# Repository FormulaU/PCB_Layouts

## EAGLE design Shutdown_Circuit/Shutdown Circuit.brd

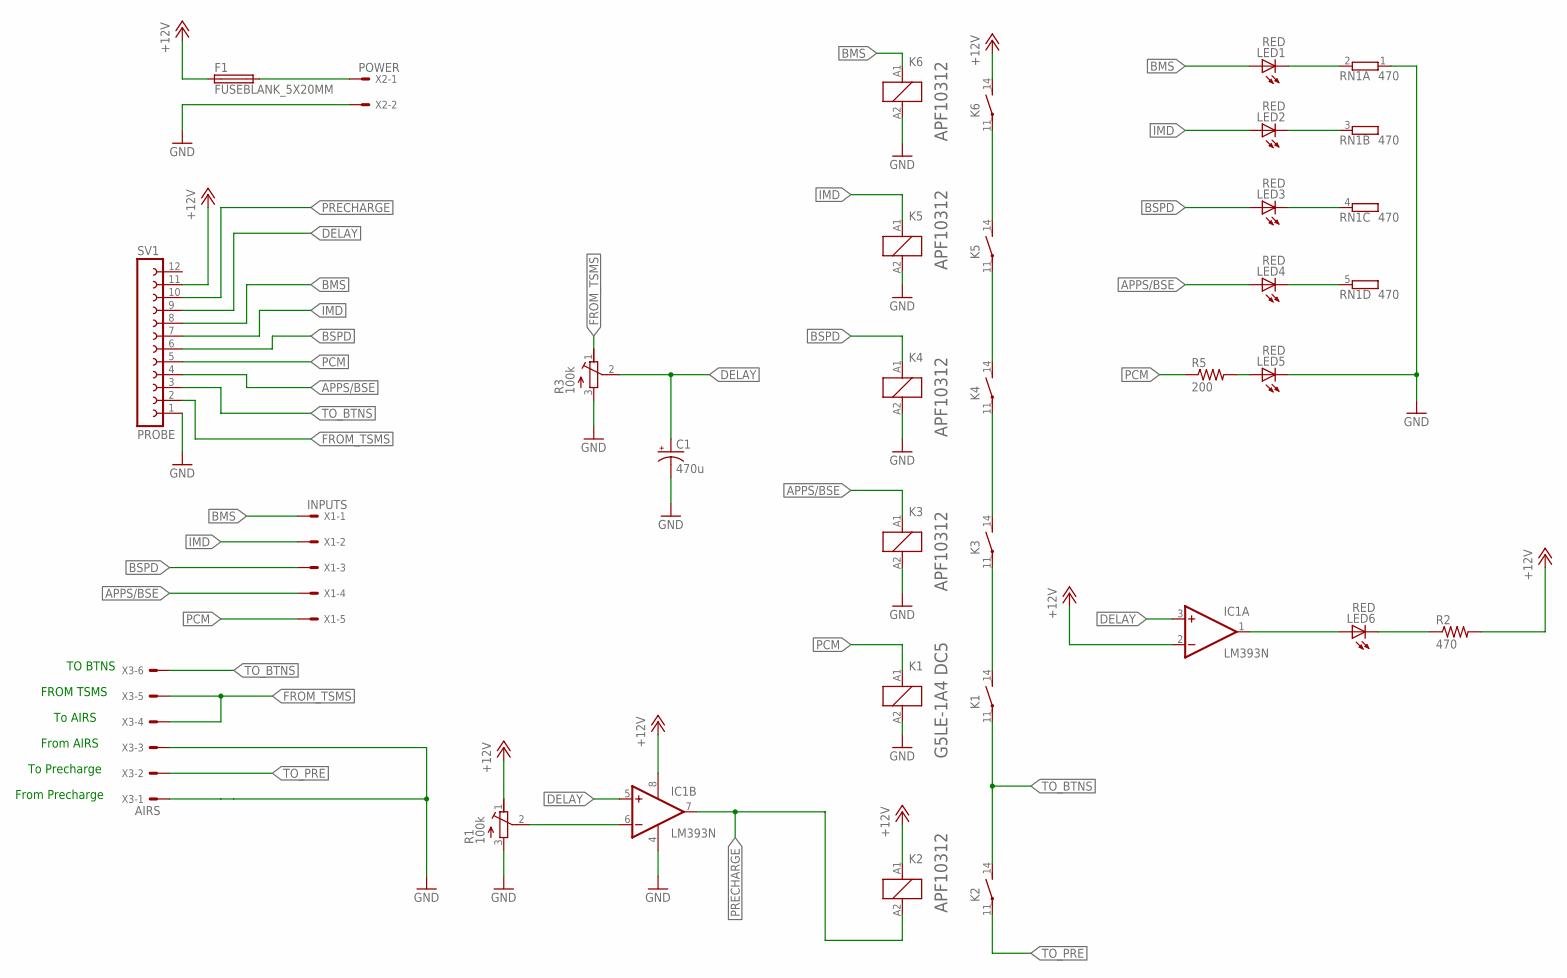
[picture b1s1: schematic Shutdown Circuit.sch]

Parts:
C1: 470u; E3,5-10
F1: FUSEBLANK_5X20MM; FUSE_HOLDER_5X20MM
IC1: LM393N; DIL08
K1: G5LE-1A4 DC5; ZN1
K2, K3, K4, K5, K6: APF10312; SNR-V1
LED1, LED2, LED3, LED4, LED5, LED6: RED; LED5MM
R1, R3: 100k; RTRIM3006P
R2: 470; 0207/10
R5: 200; 0207/10
RN1: 470; SIL5
SV1: PROBE; FE12W
X1: INPUTS; 22-23-2051
X2: POWER; 22-23-2021
X3: AIRS; 22-23-2061

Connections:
+12V: F1.1, IC1.2 (-IN), IC1.8 (V+), K2.A1 (1), K6.14 (S), R1.1 (E), R2.2, SV1.11
APPS/BSE: K3.A1 (1), LED4.A, SV1.4, X1.4
BMS: K6.A1 (1), LED1.A, SV1.8, X1.1
BSPD: K4.A1 (1), LED3.A, SV1.6, X1.3
DELAY: C1.+, IC1.3 (+IN), IC1.5 (+IN), R3.2 (S), SV1.9
FROM_TSMS: R3.1 (E), SV1.2, X3.4, X3.5
GND: C1.-, IC1.4 (V-), K1.A2 (2), K3.A2 (2), K4.A2 (2), K5.A2 (2), K6.A2 (2), LED5.K (C), R1.3 (A), R3.3 (A), RN1.1, SV1.1, X2.2, X3.1, X3.3
IMD: K5.A1 (1), LED2.A, SV1.7, X1.2
unnamed: F1.2, X2.1
unnamed: LED5.A, R5.2
unnamed: LED4.K (C), RN1.5 (2)
unnamed: LED3.K (C), RN1.4 (2)
unnamed: IC1.6 (-IN), R1.2 (S)
unnamed: LED1.K (C), RN1.2
unnamed: IC1.1 (OUT), LED6.A
unnamed: LED2.K (C), RN1.3 (2)
unnamed: K5.14 (S), K6.11
unnamed: LED6.K (C), R2.1
unnamed: K4.14 (S), K5.11
unnamed: K3.14 (S), K4.11
unnamed: K1.14 (S), K3.11
PCM: K1.A1 (1), R5.1, SV1.5, X1.5
PRECHARGE: IC1.7 (OUT), K2.A2 (2), SV1.10
TO_BTNS: K1.11, K2.14 (S), SV1.3, X3.6
TO_PRE: K2.11, X3.2

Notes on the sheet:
TO BTNS
FROM TSMS
To AIRS
From AIRS
To Precharge
From Precharge

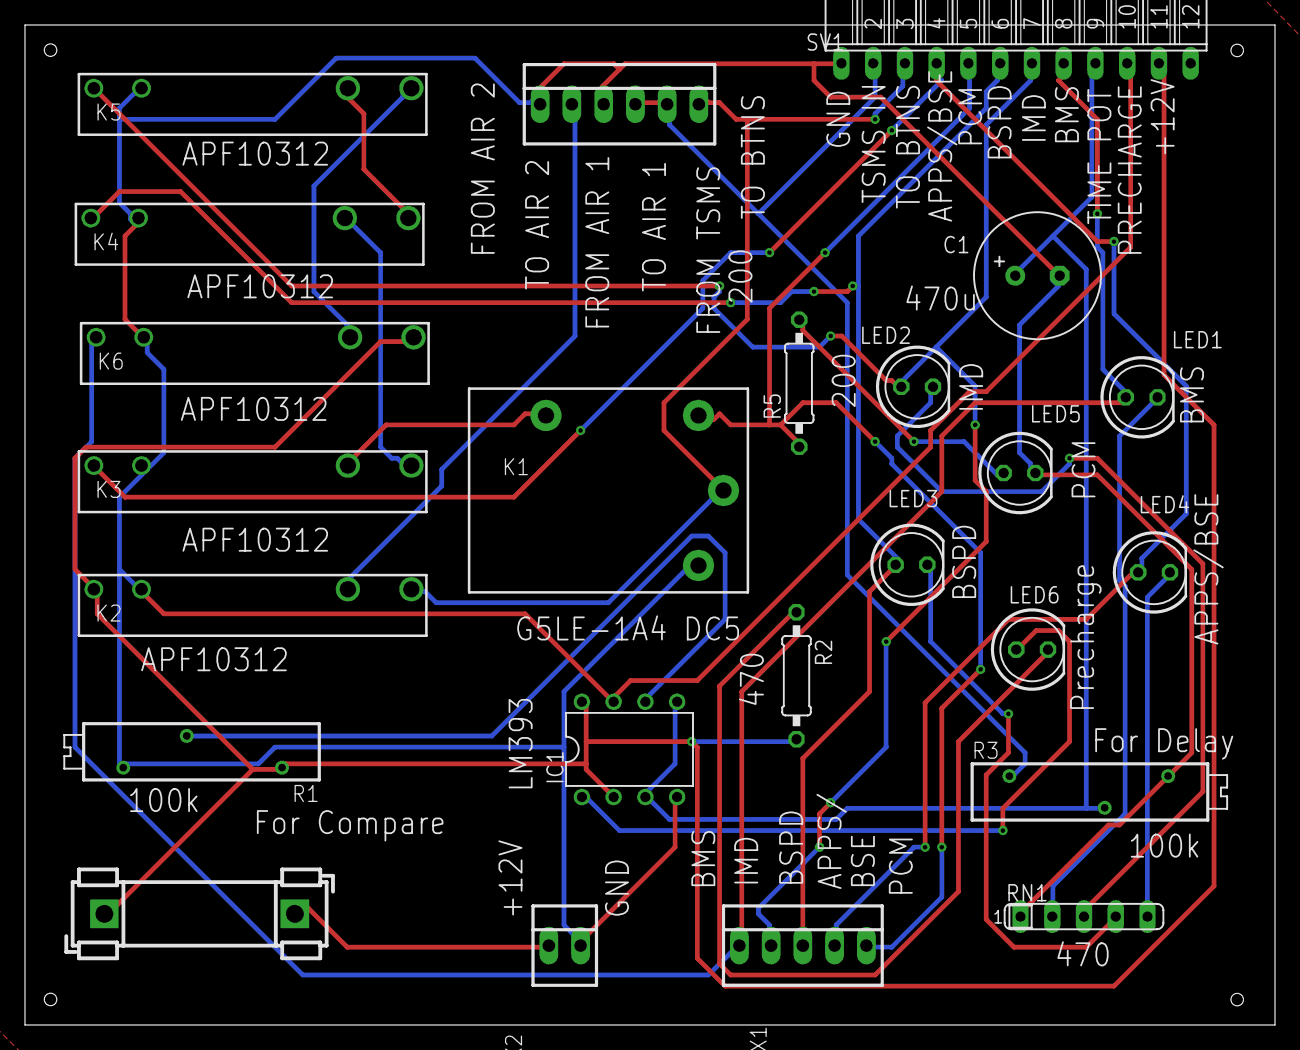
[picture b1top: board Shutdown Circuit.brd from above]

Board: 2 copper layers, 100.0 x 80.0 mm, 24 parts (0 on the bottom side), 25 nets.
